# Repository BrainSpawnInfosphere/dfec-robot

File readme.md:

# DFEC Robot

## Example Software

The example SW is written for the Arduino and is found in `robot-2` as an example.

## Hardware

Frame developed using [OpenScad](http://www.openscad.org/)

[Base plate](base.stl)

[Motor mounts](motor.stl)

## Motors

## PCB

PCB version 4 is the current version.

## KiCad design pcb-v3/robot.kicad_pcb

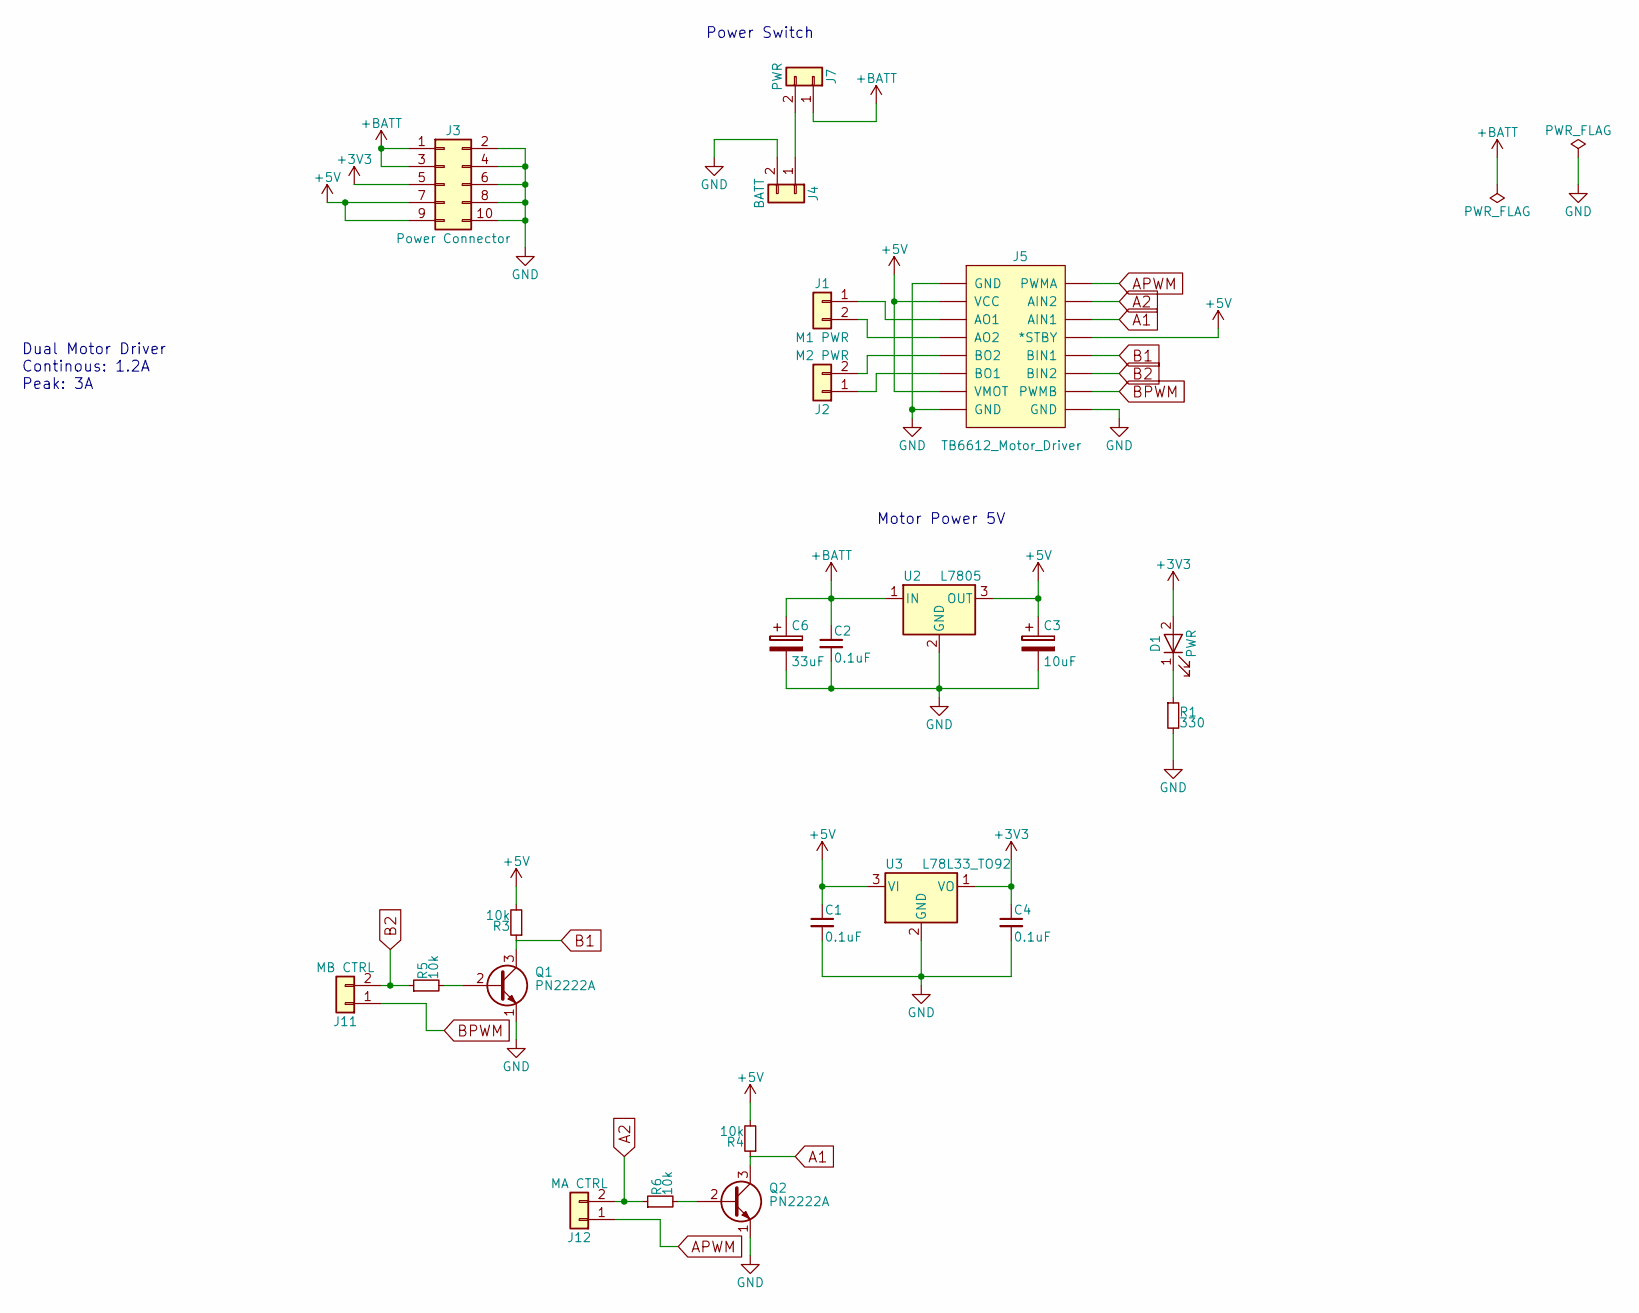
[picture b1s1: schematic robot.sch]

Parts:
C1, C2, C4: 0.1uF; C_Disc_D3.8mm_W2.6mm_P2.50mm
C3: 10uF; CP_Radial_D5.0mm_P2.00mm
C6: 33uF; CP_Radial_D5.0mm_P2.00mm
D1: PWR; LED_D3.0mm
J1: M1 PWR; Pin_Header_Straight_1x02_Pitch2.54mm
J2: M2 PWR; Pin_Header_Straight_1x02_Pitch2.54mm
J3: Power Connector; Pin_Header_Straight_2x05_Pitch2.54mm
J4: BATT; Pin_Header_Straight_1x02_Pitch2.54mm
J5: TB6612_Motor_Driver; Pololu_TB6612
J7: PWR; Pin_Header_Straight_1x02_Pitch2.54mm
J11: MB CTRL; Pin_Header_Straight_1x02_Pitch2.54mm
J12: MA CTRL; Pin_Header_Straight_1x02_Pitch2.54mm
Q1, Q2: PN2222A; TO-92_Inline_Narrow_Oval
R1: 330; R_Axial_DIN0204_L3.6mm_D1.6mm_P5.08mm_Horizontal
R3, R4, R5, R6: 10k; R_Axial_DIN0204_L3.6mm_D1.6mm_P5.08mm_Horizontal
U2: L7805; TO-220-3_Horizontal
U3: L78L33_TO92; TO-92_Inline_Narrow_Oval

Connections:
+3V3: C4.1, D1.2 (A), J3.5, U3.1 (VO)
+5V: C1.1, C3.1, J3.7, J3.9, J5.2 (VCC), J5.7 (VMOT), J5.13 (*STBY), R3.2, R4.2, U2.3 (OUT), U3.3 (VI)
+BATT: C2.1, C6.1, J3.1, J3.3, J7.1, U2.1 (IN)
A1: J5.14 (AIN1), Q2.3 (C), R4.1
A2: J5.15 (AIN2), J12.2, R6.1
APWM: J5.16 (PWMA), J12.1
B1: J5.12 (BIN1), Q1.3 (C), R3.1
B2: J5.11 (BIN2), J11.2, R5.1
BPWM: J5.10 (PWMB), J11.1
GND: C1.2, C2.2, C3.2, C4.2, C6.2, J3.2, J3.4, J3.6, J3.8, J3.10, J4.2, J5.1 (GND), J5.8 (GND), J5.9 (GND), Q1.1 (E), Q2.1 (E), R1.2, U2.2 (GND), U3.2 (GND)
unnamed: D1.1 (K), R1.1
unnamed: J1.1, J5.3 (AO1)
unnamed: J1.2, J5.4 (AO2)
unnamed: J2.1, J5.6 (BO1)
unnamed: J2.2, J5.5 (BO2)
unnamed: J4.1, J7.2
unnamed: Q1.2 (B), R5.2
unnamed: Q2.2 (B), R6.2

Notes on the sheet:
Power Switch
Motor Power 5V
Dual Motor Driver Continous: 1.2A Peak: 3A

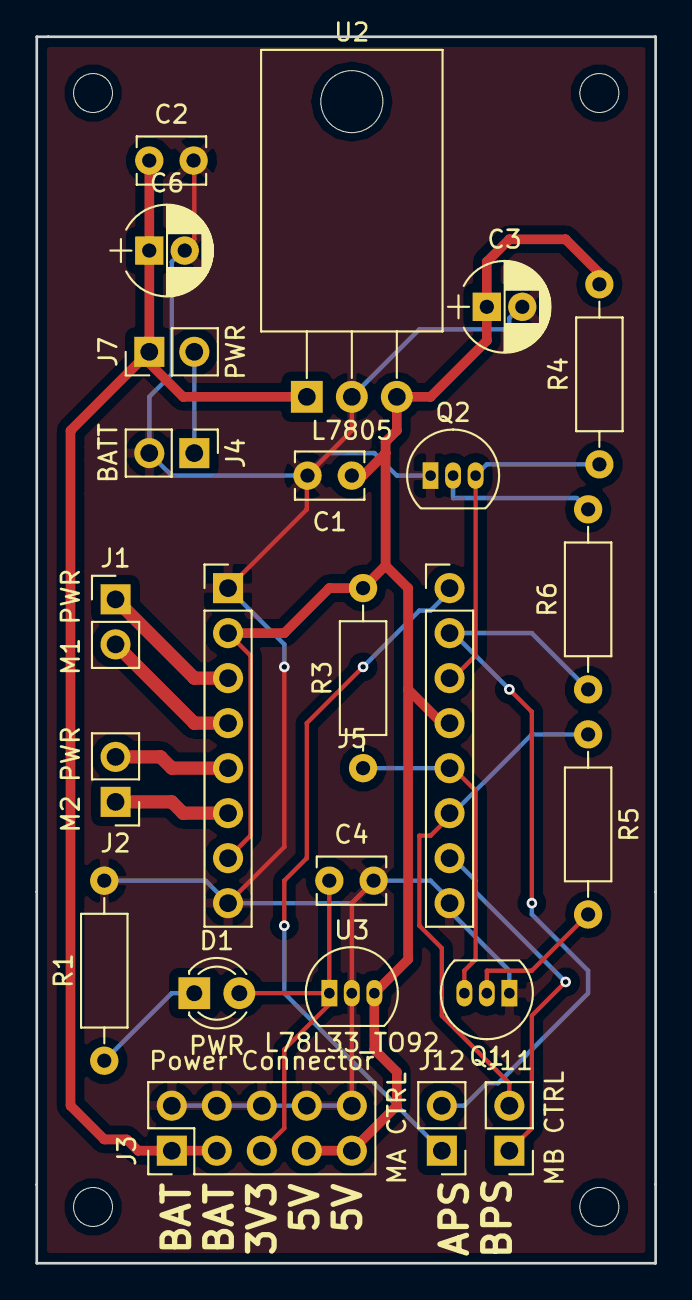
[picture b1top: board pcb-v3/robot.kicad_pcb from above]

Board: 2 copper layers, 34.9 x 69.2 mm, 23 parts (0 on the bottom side), 18 nets.

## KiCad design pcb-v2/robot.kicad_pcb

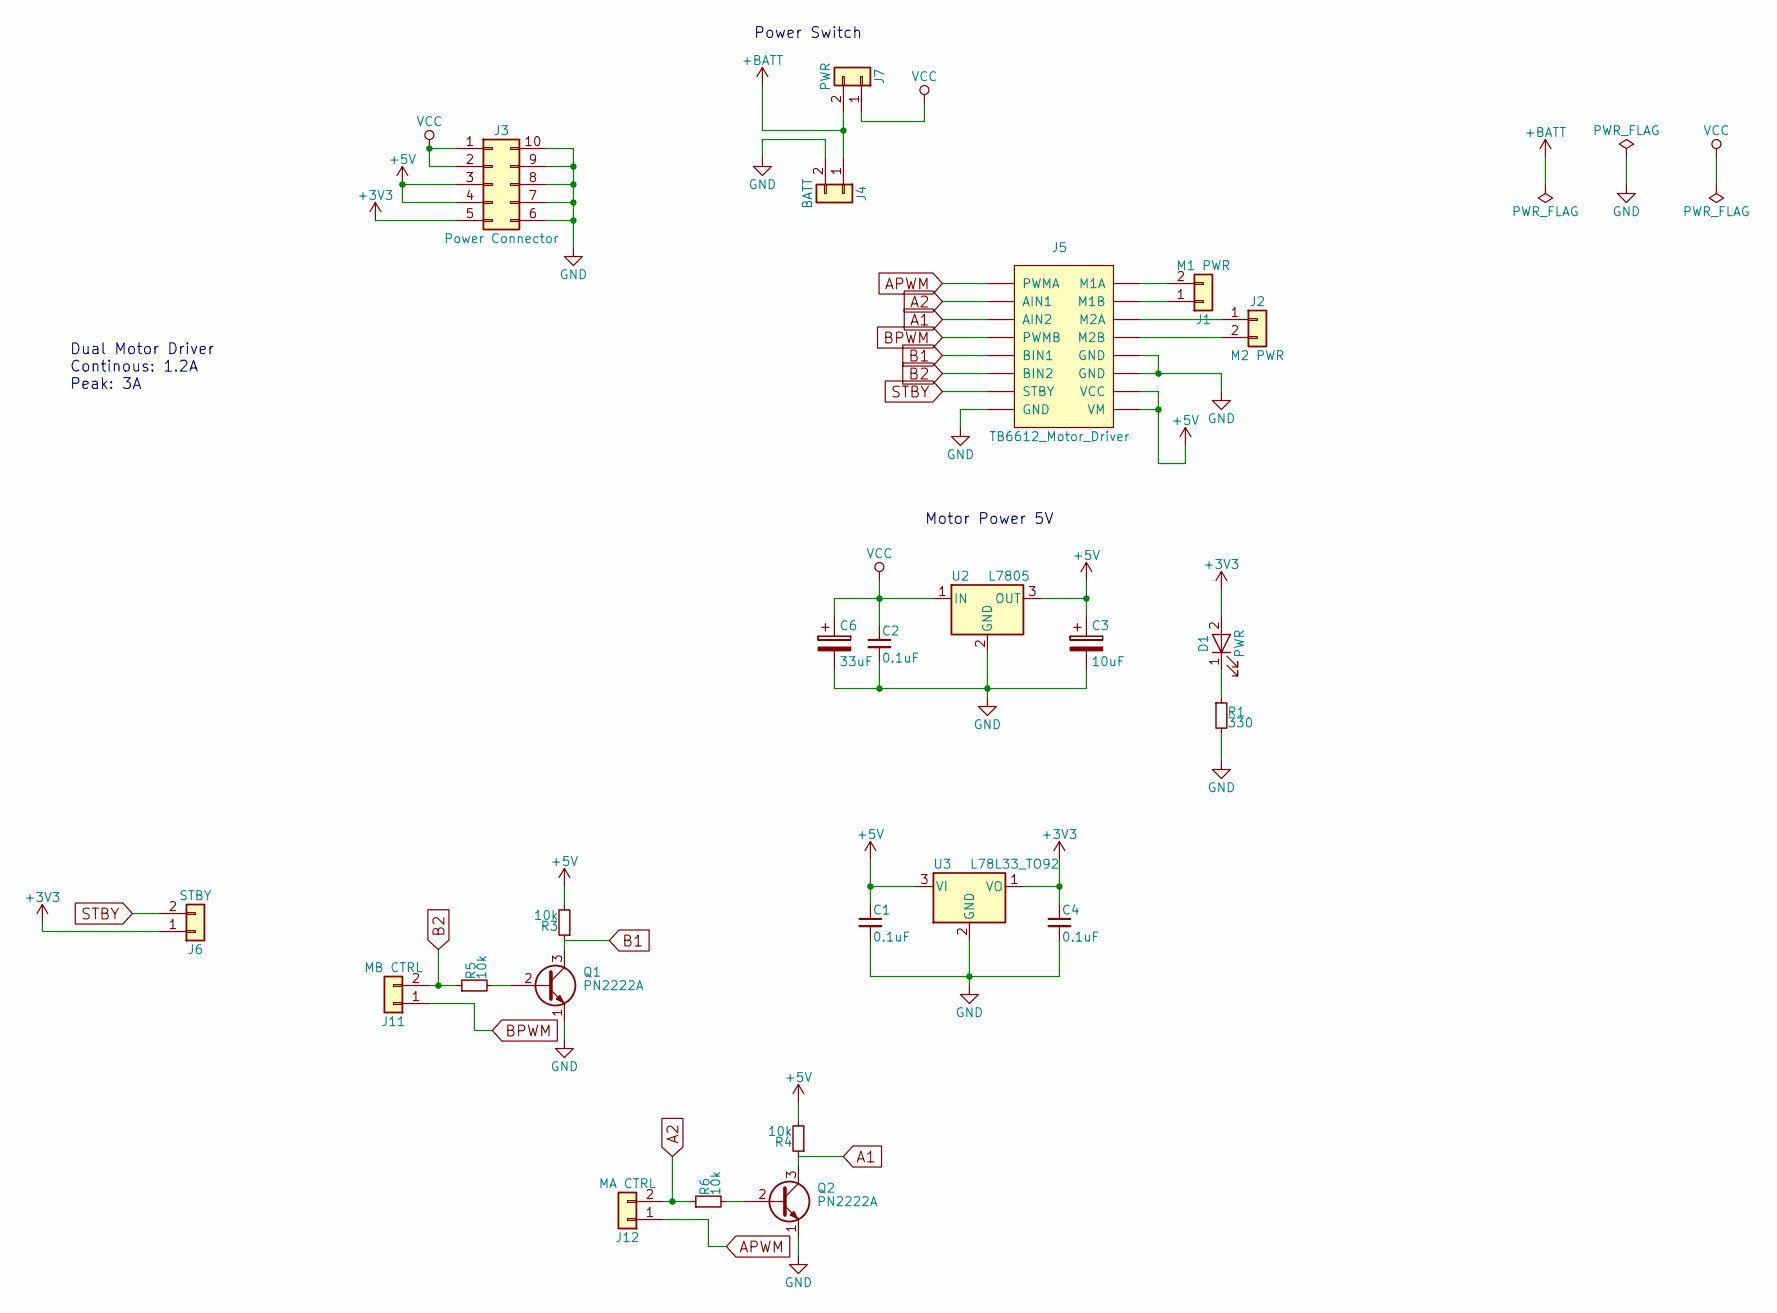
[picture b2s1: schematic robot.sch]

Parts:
C1, C2, C4: 0.1uF; C_Disc_D3.8mm_W2.6mm_P2.50mm
C3: 10uF; CP_Radial_D5.0mm_P2.00mm
C6: 33uF; CP_Radial_D5.0mm_P2.00mm
D1: PWR; LED_D3.0mm
J1: M1 PWR; Pin_Header_Straight_1x02_Pitch2.54mm
J2: M2 PWR; Pin_Header_Straight_1x02_Pitch2.54mm
J3: Power Connector; Pin_Header_Straight_2x05_Pitch2.54mm
J4: BATT; Pin_Header_Straight_1x02_Pitch2.54mm
J5: TB6612_Motor_Driver; Pololu_TB6612
J6: STBY; Pin_Header_Straight_1x02_Pitch2.54mm
J7: PWR; Pin_Header_Straight_1x02_Pitch2.54mm
J11: MB CTRL; Pin_Header_Straight_1x02_Pitch2.54mm
J12: MA CTRL; Pin_Header_Straight_1x02_Pitch2.54mm
Q1, Q2: PN2222A; TO-92_Inline_Narrow_Oval
R1: 330; R_Axial_DIN0204_L3.6mm_D1.6mm_P5.08mm_Horizontal
R3, R4, R5, R6: 10k; R_Axial_DIN0204_L3.6mm_D1.6mm_P5.08mm_Horizontal
U2: L7805; TO-220-3_Horizontal
U3: L78L33_TO92; TO-92_Inline_Narrow_Oval

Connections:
+3V3: C4.1, D1.2 (A), J3.5, J6.1, U3.1 (VO)
+5V: C1.1, C3.1, J3.3, J3.4, J5.9 (VM), J5.10 (VCC), R3.2, R4.2, U2.3 (OUT), U3.3 (VI)
+BATT: J4.1, J7.2
A1: J5.3 (AIN2), Q2.3 (C), R4.1
A2: J5.2 (AIN1), J12.2, R6.1
APWM: J5.1 (PWMA), J12.1
B1: J5.5 (BIN1), Q1.3 (C), R3.1
B2: J5.6 (BIN2), J11.2, R5.1
BPWM: J5.4 (PWMB), J11.1
GND: C1.2, C2.2, C3.2, C4.2, C6.2, J3.6, J3.7, J3.8, J3.9, J3.10, J4.2, J5.8 (GND), J5.11 (GND), J5.12 (GND), Q1.1 (E), Q2.1 (E), R1.2, U2.2 (GND), U3.2 (GND)
unnamed: D1.1 (K), R1.1
unnamed: J1.1, J5.15 (M1B)
unnamed: J1.2, J5.16 (M1A)
unnamed: J2.1, J5.14 (M2A)
unnamed: J2.2, J5.13 (M2B)
unnamed: Q1.2 (B), R5.2
unnamed: Q2.2 (B), R6.2
STBY: J5.7 (STBY), J6.2
VCC: C2.1, C6.1, J3.1, J3.2, J7.1, U2.1 (IN)

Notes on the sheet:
Power Switch
Motor Power 5V
Dual Motor Driver Continous: 1.2A Peak: 3A

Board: 2 copper layers, 24 parts (0 on the bottom side), 19 nets, no tracks yet.

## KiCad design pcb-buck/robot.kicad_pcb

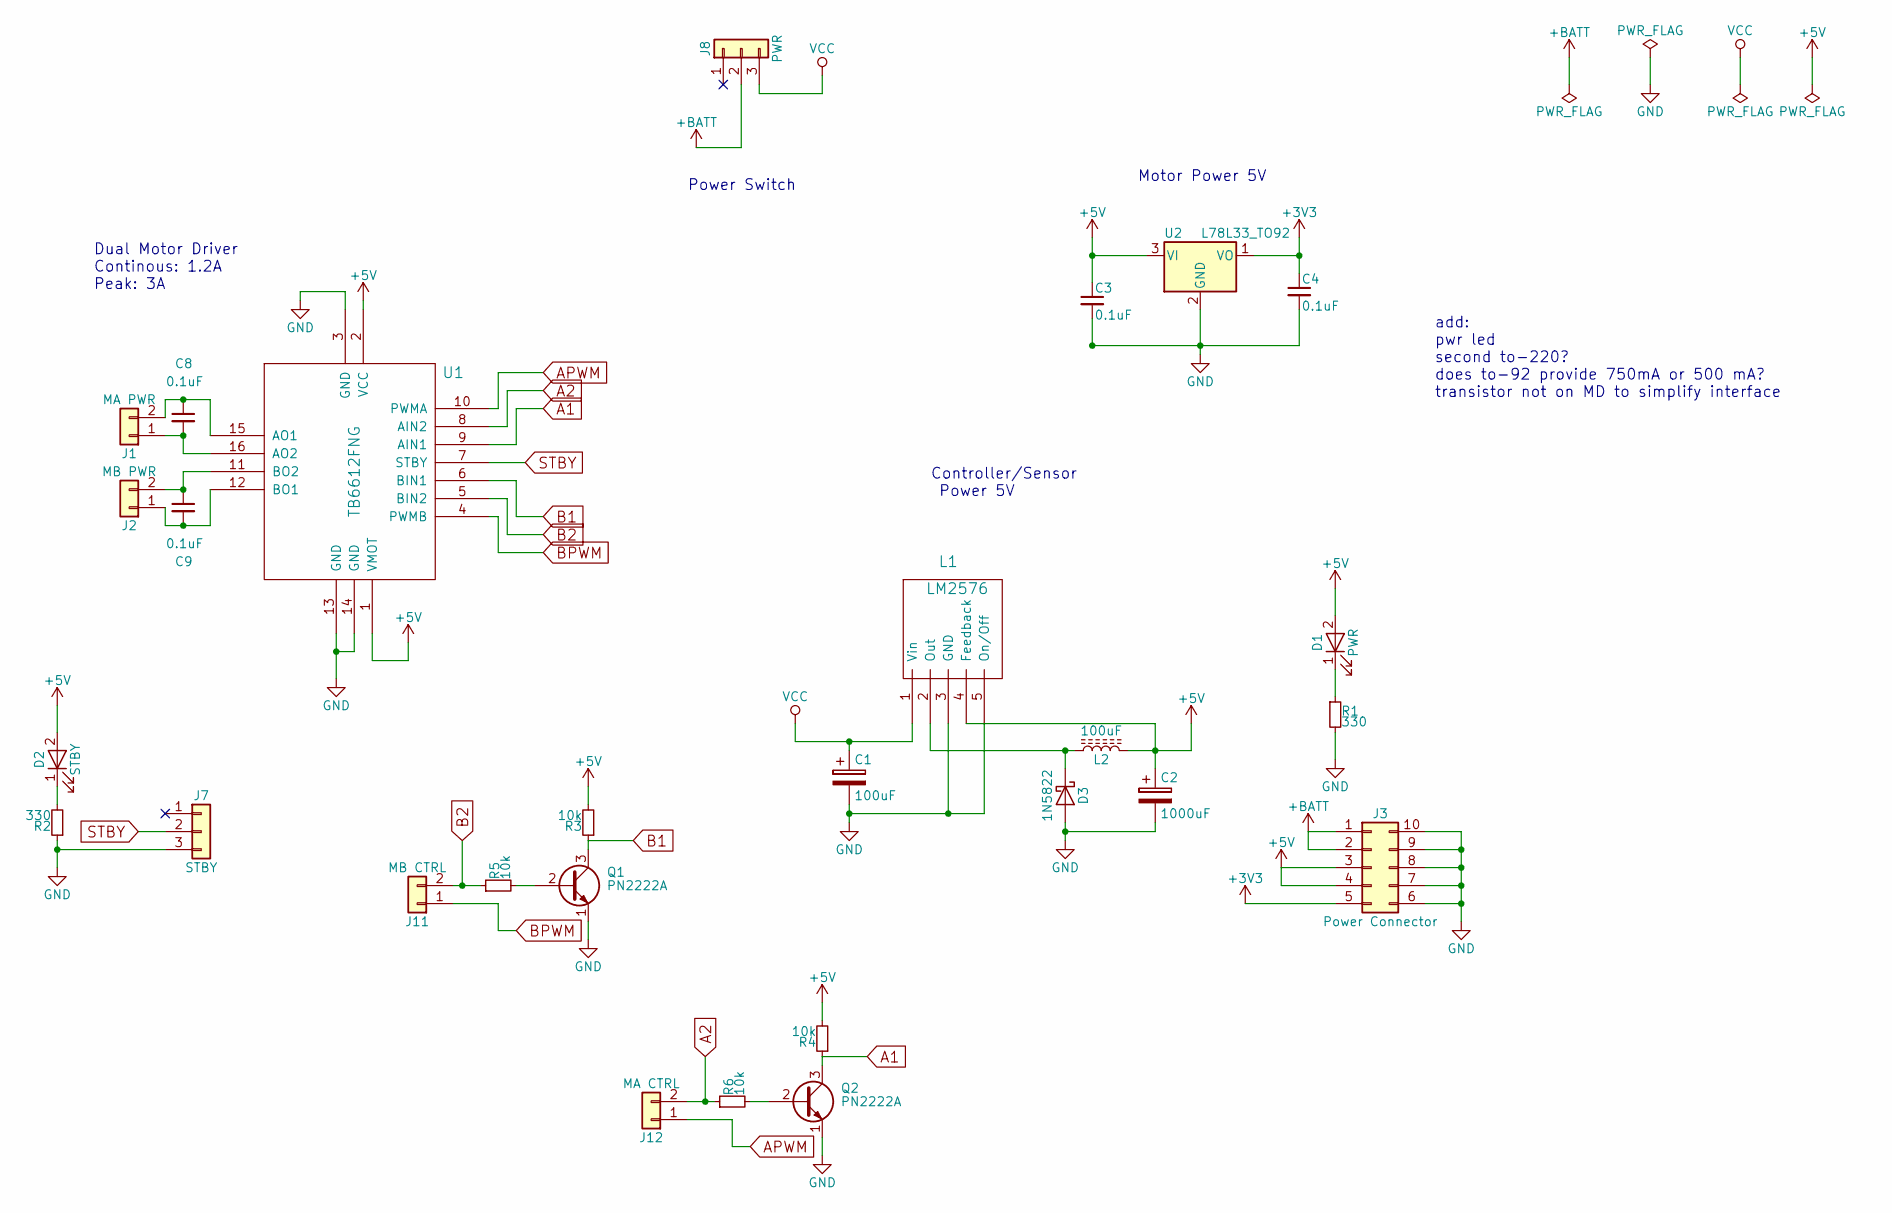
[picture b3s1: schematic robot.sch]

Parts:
C1: 100uF; CP_Radial_D5.0mm_P2.00mm
C2: 1000uF; CP_Radial_D5.0mm_P2.00mm
C3, C4, C8, C9: 0.1uF; C_Disc_D3.8mm_W2.6mm_P2.50mm
D1: PWR; LED_D3.0mm
D2: STBY; LED_D3.0mm
D3: 1N5822; D_A-405_P12.70mm_Horizontal
J1: MA PWR; Pin_Header_Straight_1x02_Pitch2.54mm
J2: MB PWR; Pin_Header_Straight_1x02_Pitch2.54mm
J3: Power Connector; Pin_Header_Straight_2x05_Pitch2.54mm
J7: STBY; Pin_Header_Straight_1x03_Pitch2.54mm
J8: PWR; Pin_Header_Straight_1x03_Pitch2.54mm
J11: MB CTRL; Pin_Header_Straight_1x02_Pitch2.54mm
J12: MA CTRL; Pin_Header_Straight_1x02_Pitch2.54mm
L1: LM2576; TO-220-5_Horizontal
L2: 100uF; L_Radial_D18.0mm_P10.00mm
Q1, Q2: PN2222A; TO-92_Molded_Narrow
R1, R2: 330; R_Axial_DIN0204_L3.6mm_D1.6mm_P5.08mm_Horizontal
R3, R4, R5, R6: 10k; R_Axial_DIN0204_L3.6mm_D1.6mm_P5.08mm_Horizontal
U1: TB6612FNG; Adafruit_Motor_Driver_TB6612
U2: L78L33_TO92; TO-92_Inline_Narrow_Oval

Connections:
+3V3: C4.1, J3.5, U2.1 (VO)
+5V: C2.1, C3.1, D1.2 (A), D2.2 (A), J3.3, J3.4, L1.4 (Feedback), L2.2, R3.2, R4.2, U1.1 (VMOT), U1.2 (VCC), U2.3 (VI)
+BATT: J3.1, J3.2, J8.2
A1: Q2.3 (C), R4.1, U1.9 (AIN1)
A2: J12.2, R6.1, U1.8 (AIN2)
APWM: J12.1, U1.10 (PWMA)
B1: Q1.3 (C), R3.1, U1.6 (BIN1)
B2: J11.2, R5.1, U1.5 (BIN2)
BPWM: J11.1, U1.4 (PWMB)
GND: C1.2, C2.2, C3.2, C4.2, D3.2 (A), J3.6, J3.7, J3.8, J3.9, J3.10, J7.3, L1.3 (GND), L1.5 (On/Off), Q1.1 (E), Q2.1 (E), R1.2, R2.1, U1.3 (GND), U1.13 (GND), U1.14 (GND), U2.2 (GND)
unnamed: C8.1, J1.2, U1.15 (AO1)
unnamed: C8.2, J1.1, U1.16 (AO2)
unnamed: C9.1, J2.2, U1.11 (BO2)
unnamed: C9.2, J2.1, U1.12 (BO1)
unnamed: D1.1 (K), R1.1
unnamed: D2.1 (K), R2.2
unnamed: D3.1 (K), L1.2 (Out), L2.1
unnamed: Q1.2 (B), R5.2
unnamed: Q2.2 (B), R6.2
STBY: J7.2, U1.7 (STBY)
VCC: C1.1, J8.3, L1.1 (Vin)

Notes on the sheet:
add: pwr led second to-220? does to-92 provide 750mA or 500 mA? transistor not on MD to simplify interface
Power Switch
Motor Power 5V
Controller/Sensor Power 5V
Dual Motor Driver Continous: 1.2A Peak: 3A

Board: 2 copper layers, 28 parts (0 on the bottom side), 21 nets, no tracks yet.

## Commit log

2018-03-12 close to working
2018-04-15 new version
2018-04-16 fixed md footprint and 1/4 w resistors
2018-04-16 small fixes
2018-05-11 hardware
2018-05-14 more design mods
2018-05-19 Create deleteme
